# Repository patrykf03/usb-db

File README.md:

# Pats pseudo squatterboard

Tldr:
* udb pinout
* 2 m.2 mountpoints
* sideways usb
* should just barely work
* Adapted from the squatterboard

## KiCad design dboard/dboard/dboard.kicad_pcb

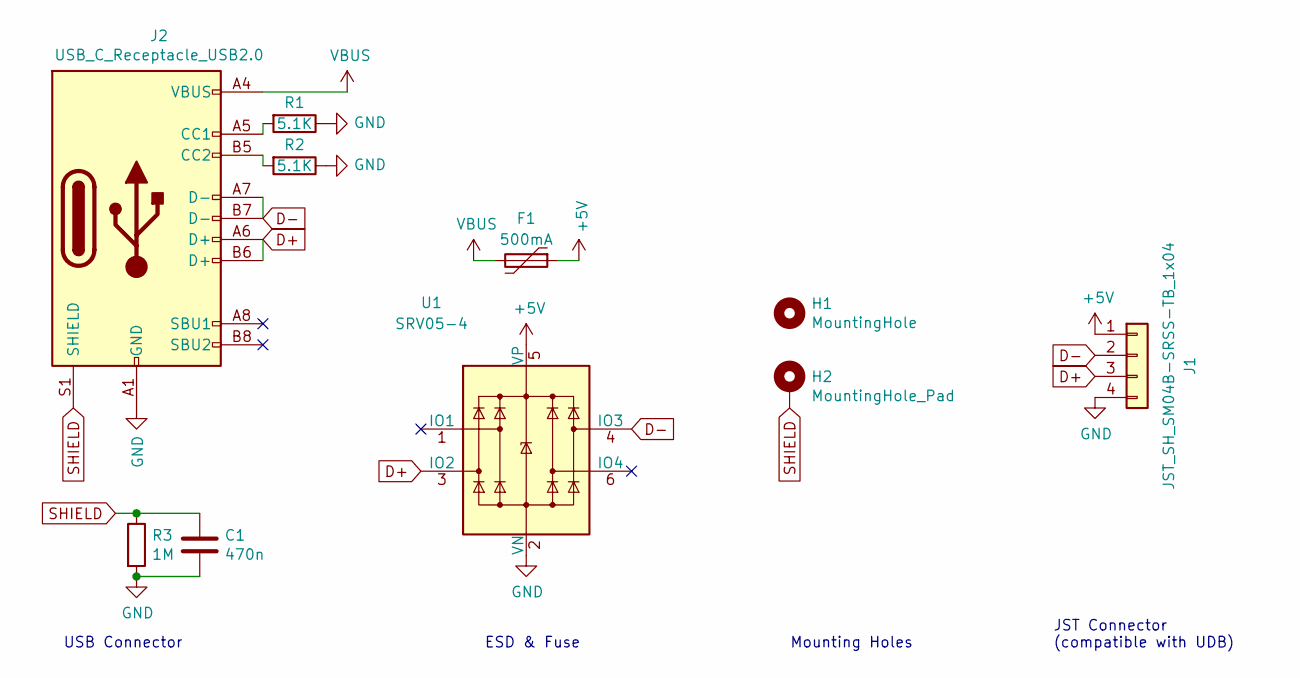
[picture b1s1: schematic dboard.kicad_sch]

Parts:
C1: 470n; C_0805_2012Metric; jlc C13967
F1: 500mA; Fuse_1206_3216Metric; jlc C70076
H1: MountingHole; MountingHole_2.2mm_M2_DIN965_Pad
H2: MountingHole_Pad; MountingHole_2.2mm_M2_DIN965_Pad
J1: JST_SH_SM04B-SRSS-TB_1x04; JST_SH_SM04B-SRSS-TB_1x04-1MP_P1.00mm_Horizontal
J2: USB_C_Receptacle_USB2.0; USB_C_Receptacle_HRO_TYPE-C-31-M-12
R1, R2: 5.1K; R_0603_1608Metric; jlc C23186
R3: 1M; R_1206_3216Metric; jlc C17927
U1: SRV05-4; SOT-23-6; jlc C85364

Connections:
+5V: F1.1, J1.1, U1.5 (VP)
D+: J1.3, J2.A6 (D+), J2.B6 (D+), U1.3 (IO2)
D-: J1.2, J2.A7 (D-), J2.B7 (D-), U1.4 (IO3)
GND: C1.2, J1.4, J2.A1 (GND), J2.A12 (GND), J2.B1 (GND), J2.B12 (GND), R1.1, R2.1, R3.2, U1.2 (VN)
unnamed: J2.A5 (CC1), R1.2
unnamed: J2.B5 (CC2), R2.2
SHIELD: C1.1, H2.1, J2.S1 (SHIELD), R3.1
VBUS: F1.2, J2.A4 (VBUS), J2.A9 (VBUS), J2.B4 (VBUS), J2.B9 (VBUS)

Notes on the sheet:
USB Connector
ESD & Fuse
Mounting Holes
JST Connector (compatible with UDB)

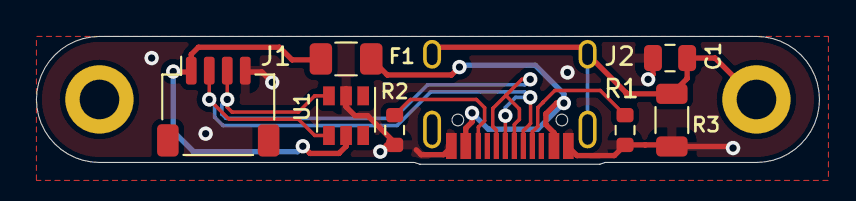
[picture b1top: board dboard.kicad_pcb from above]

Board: 2 copper layers, 43.5 x 7.1 mm, 11 parts (0 on the bottom side), 8 nets.

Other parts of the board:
Ref**: Val**; tt_4mm

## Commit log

2022-05-24 Add all the shit lmao
2022-05-24 apparently shit didnt get added in
